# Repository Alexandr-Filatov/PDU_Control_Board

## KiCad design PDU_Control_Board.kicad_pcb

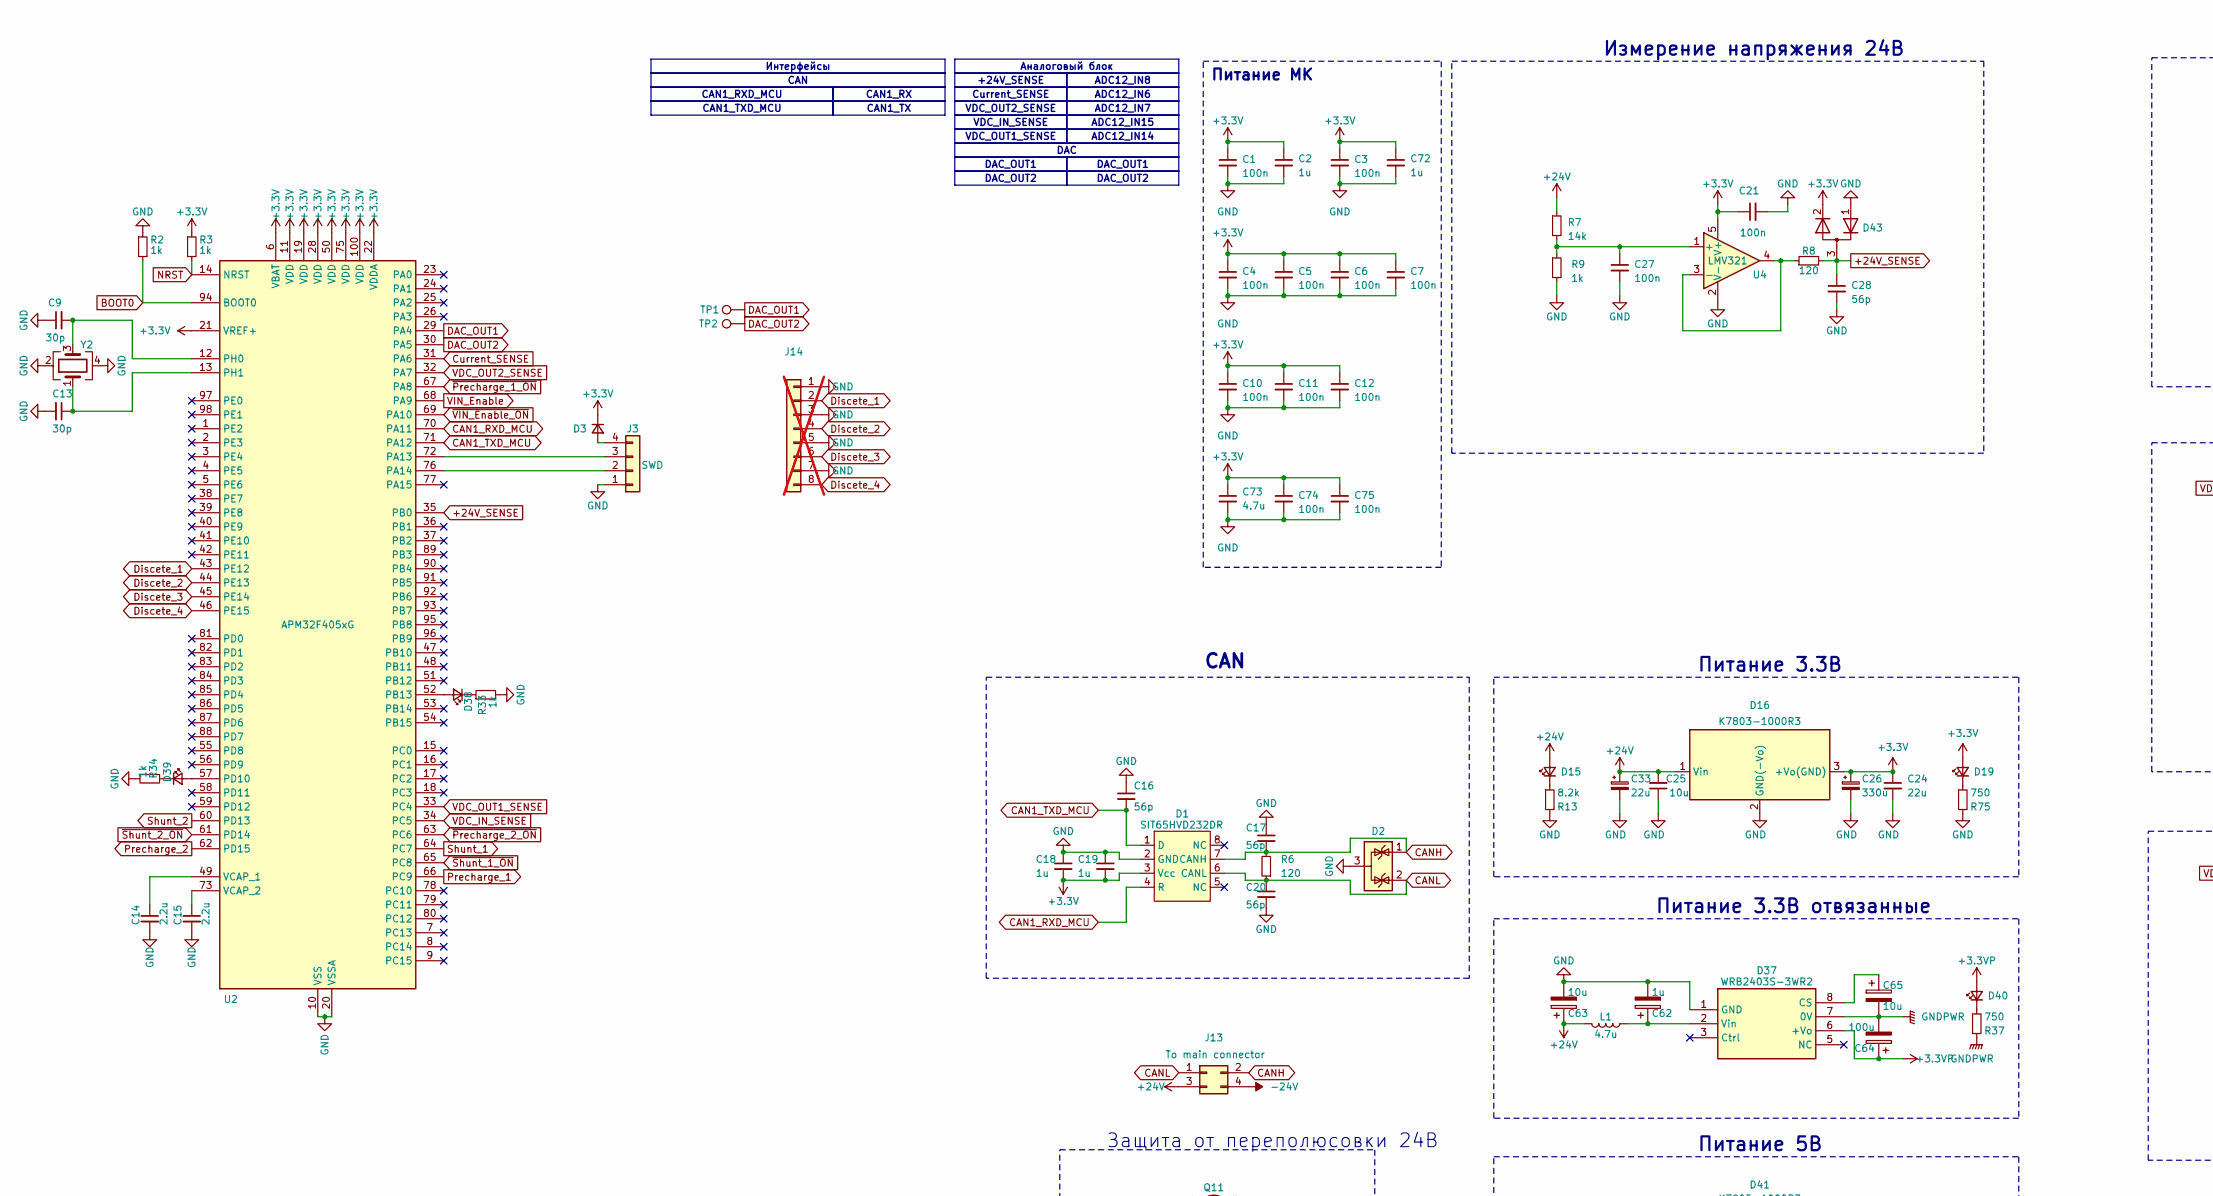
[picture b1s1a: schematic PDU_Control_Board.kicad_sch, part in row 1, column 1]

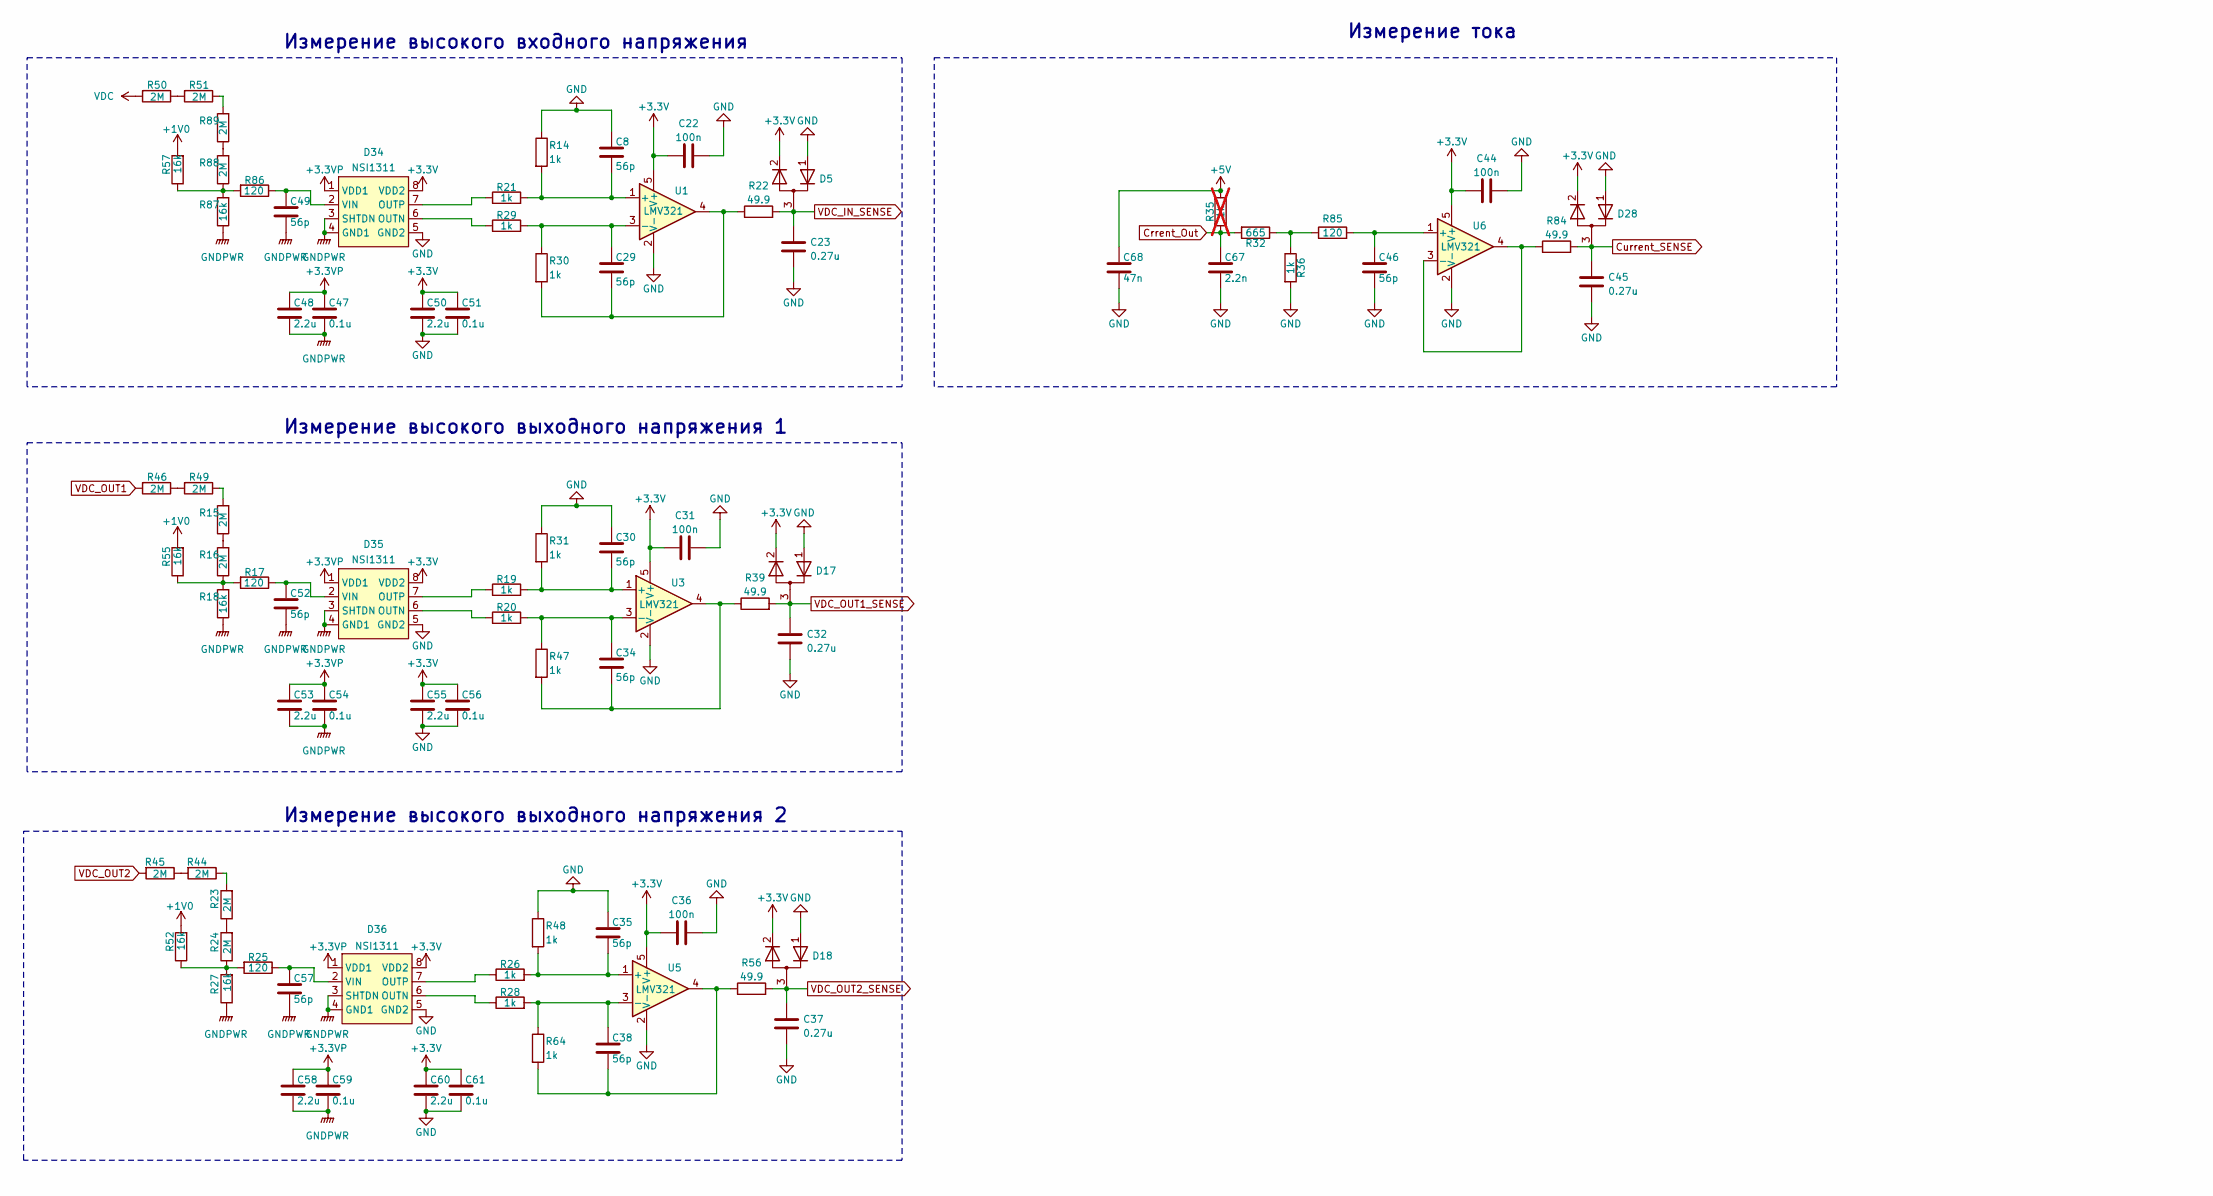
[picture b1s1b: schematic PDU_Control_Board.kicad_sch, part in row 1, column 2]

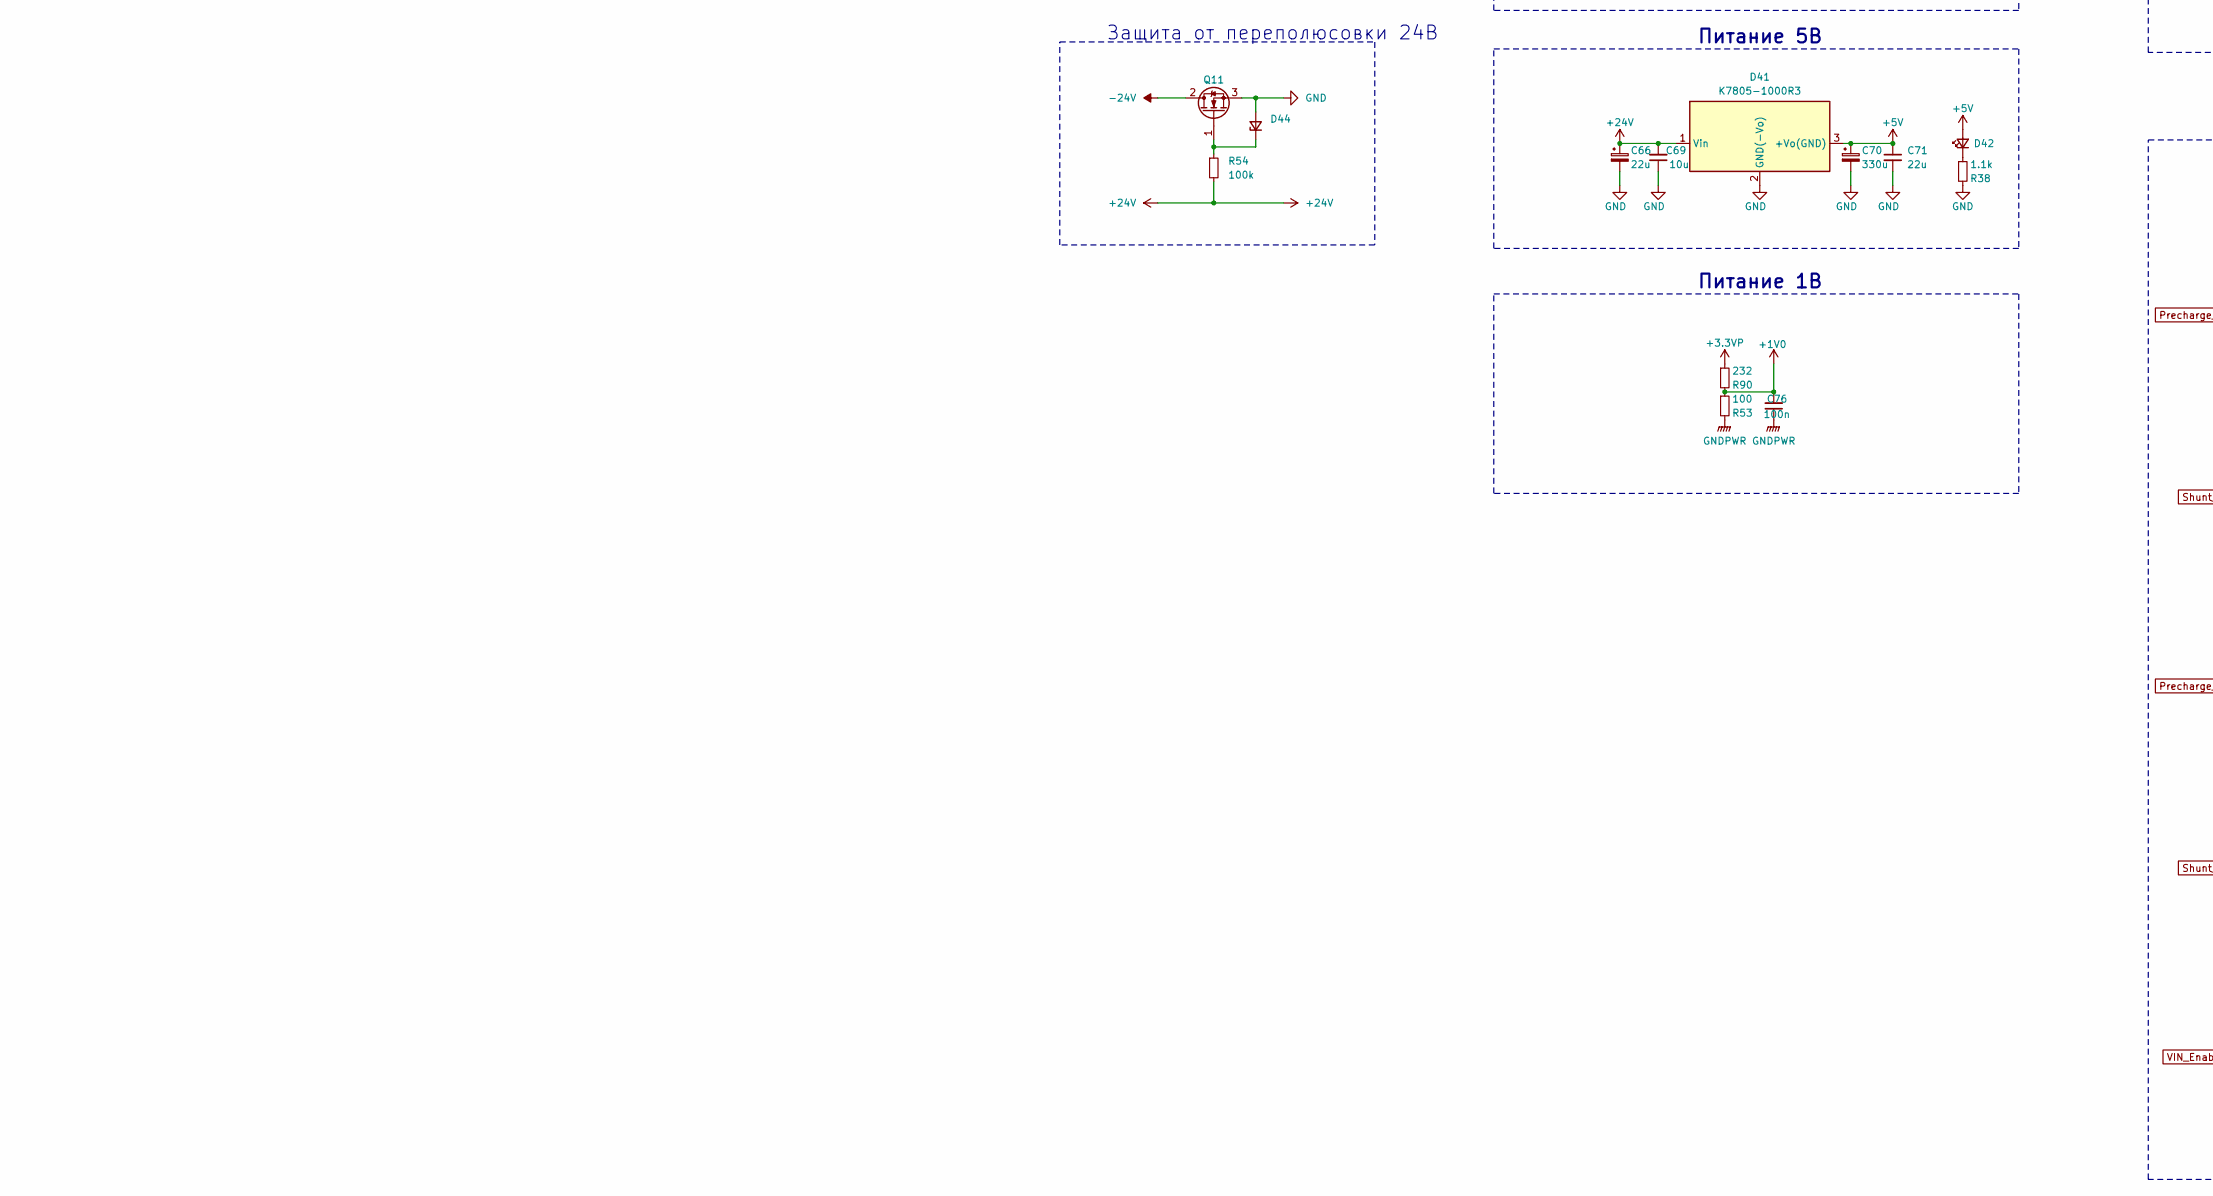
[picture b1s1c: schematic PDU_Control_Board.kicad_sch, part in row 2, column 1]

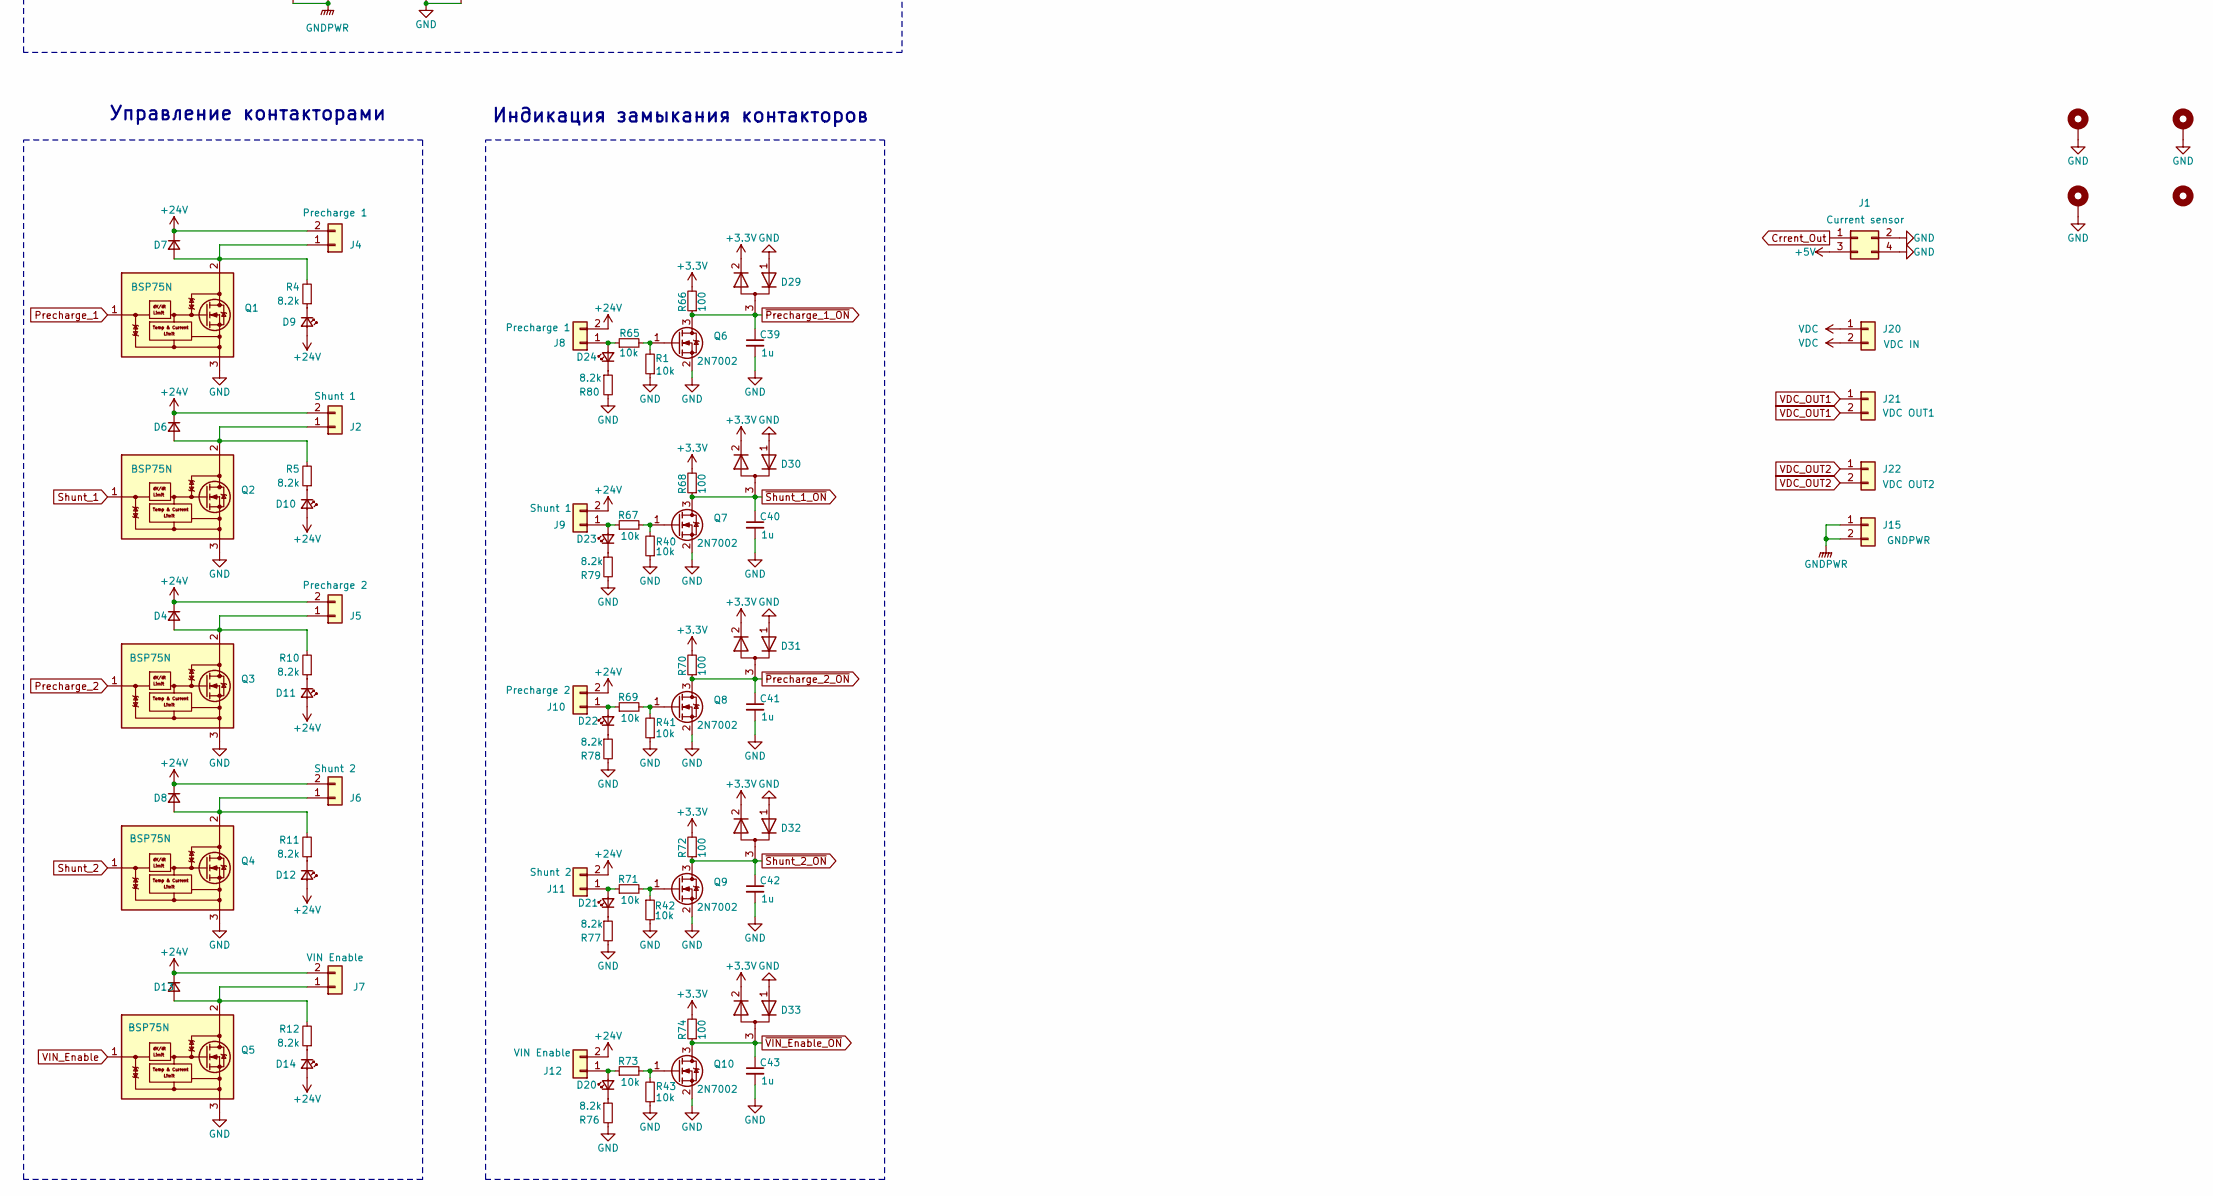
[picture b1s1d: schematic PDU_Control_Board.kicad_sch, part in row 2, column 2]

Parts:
C1, C3, C4, C5, C6, C7, C10, C11, C12, C21, C22, C27, C31, C36, C44, C74, C75, C76: 100n; C_0805_2012Metric_Pad1.18x1.45mm_HandSolder
C2, C18, C19, C39, C40, C41, C42, C43, C72: 1u; C_0805_2012Metric_Pad1.18x1.45mm_HandSolder
C8, C16, C17, C20, C28, C29, C30, C34, C35, C38, C46, C49, C52, C57: 56p; C_0805_2012Metric_Pad1.18x1.45mm_HandSolder
C9, C13: 30p; C_0805_2012Metric_Pad1.18x1.45mm_HandSolder
C14, C15, C48, C50, C53, C55, C58, C60: 2.2u; C_0805_2012Metric_Pad1.18x1.45mm_HandSolder
C23, C32, C37, C45: 0.27u; C_0805_2012Metric_Pad1.18x1.45mm_HandSolder
C24, C71: 22u; C_1210_3225Metric_Pad1.33x2.70mm_HandSolder
C25, C69: 10u; C_1210_3225Metric_Pad1.33x2.70mm_HandSolder
C26, C70: 330u; CP_EIA-6032-28_Kemet-C_Pad2.25x2.35mm_HandSolder
C33, C66: 22u; CP_EIA-7343-43_Kemet-X_Pad2.25x2.55mm_HandSolder
C47, C51, C54, C56, C59, C61: 0.1u; C_0805_2012Metric_Pad1.18x1.45mm_HandSolder
C62: 1u; CP_EIA-6032-28_Kemet-C_Pad2.25x2.35mm_HandSolder
C63: 10u; CP_EIA-7360-38_Kemet-E_Pad2.25x4.25mm_HandSolder
C64: 100u; CP_EIA-3528-21_Kemet-B_Pad1.50x2.35mm_HandSolder
C65: 10u; CP_EIA-3528-21_Kemet-B_Pad1.50x2.35mm_HandSolder
C67: 2.2n; C_0805_2012Metric_Pad1.18x1.45mm_HandSolder
C68: 47n; C_0805_2012Metric_Pad1.18x1.45mm_HandSolder
C73: 4.7u; C_0805_2012Metric_Pad1.18x1.45mm_HandSolder
D1: SOIC-8_3.9x4.9mm_P1.27mm
D2, D5, D17, D18, D28, D29, D30, D31, D32, D33, D43: SOT-23
D3: D_SOD-323_HandSoldering
D4, D6, D7, D8, D13: D_SMA_Handsoldering
D9, D10, D11, D12, D14, D15, D19, D20, D21, D22, D23, D24, D38, D39, D40, D42: LED_0805_2012Metric
D16, D41: K78xx-1000R3
D34, D35, D36: SOIC-8_7.5x5.85mm_P1.27mm
D37: WRB_S-3WR2
D44: D_SOD-123
H1, H2, H3: MountingHole_Pad; MountingHole_4.3mm_M4_Pad_Via
H4: MountingHole; MountingHole_4.3mm_M4
J1, J13: Molex_Mini-Fit_Jr_5566-04A_2x02_P4.20mm_Vertical
J2, J4, J5, J6, J7, J8, J9, J10, J11, J12, J15, J20, J21, J22: Mini-Fit_01x02_Vertical
J3: PinHeader_1x04_P2.54mm_Vertical
J14: PinHeader_2x04_P2.54mm_Vertical; not fitted
L1: 4.7u; L_1812_4532Metric_Pad1.30x3.40mm_HandSolder
Q1, Q2, Q3, Q4, Q5: SOT-223
Q6, Q7, Q8, Q9, Q10: SOT-23
Q11: TO-252-2
R1, R40, R41, R42, R43, R65, R67, R69, R71, R73: 10k; R_0805_2012Metric_Pad1.20x1.40mm_HandSolder
R2, R3, R9, R14, R19, R20, R21, R26, R28, R29, R30, R31, R33, R34, R36, R47, R48, R64: 1k; R_0805_2012Metric_Pad1.20x1.40mm_HandSolder
R4, R5, R10, R11, R12, R13, R76, R77, R78, R79, R80: 8.2k; R_0805_2012Metric_Pad1.20x1.40mm_HandSolder
R6, R8, R17, R25, R85, R86: 120; R_0805_2012Metric_Pad1.20x1.40mm_HandSolder
R7: 14k; R_0805_2012Metric_Pad1.20x1.40mm_HandSolder
R15, R16, R23, R24, R44, R45, R46, R49, R50, R51, R88, R89: 2M; R_1206_3216Metric
R18, R27, R52, R55, R57, R87: 16k; R_1206_3216Metric
R22, R39, R56, R84: 49.9; R_0805_2012Metric_Pad1.20x1.40mm_HandSolder
R32: 665; R_0805_2012Metric_Pad1.20x1.40mm_HandSolder
R35: 1k; R_0805_2012Metric_Pad1.20x1.40mm_HandSolder; not fitted
R37, R75: 750; R_0805_2012Metric_Pad1.20x1.40mm_HandSolder
R38: 1.1k; R_0805_2012Metric_Pad1.20x1.40mm_HandSolder
R53, R66, R68, R70, R72, R74: 100; R_0805_2012Metric_Pad1.20x1.40mm_HandSolder
R54: 100k; R_0805_2012Metric_Pad1.20x1.40mm_HandSolder
R90: 232; R_0805_2012Metric_Pad1.20x1.40mm_HandSolder
TP1, TP2: TestPoint; TestPoint_Loop_D1.80mm_Drill1.0mm_Beaded
U1, U3, U4, U5, U6: SOT-23-5
U2: LQFP-100_14x14mm_P0.5mm
Y2: Crystal_SMD_SeikoEpson_FA238-4Pin_3.2x2.5mm

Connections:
+1V0: C76.2, R52.2, R53.1, R55.2, R57.2, R90.2
+3.3V: C1.1, C2.1, C3.1, C4.1, C5.1, C6.1, C7.1, C10.1, C11.1, C12.1, C18.2, C19.2, C21.1, C22.1, C24.1, C26.1, C31.1, C36.1, C44.1, C50.2, C51.1, C55.2, C56.1, C60.2, C61.1, C72.1, C73.1, C74.1, C75.1, D1.3 (Vcc), D3.1 (K), D5.2 (K), D16.3 (+Vo(GND)), D17.2 (K), D18.2 (K), D19.2 (A), D28.2 (K), D29.2 (K), D30.2 (K), D31.2 (K), D32.2 (K), D33.2 (K), D34.8 (VDD2), D35.8 (VDD2), D36.8 (VDD2), D43.2 (K), R3.1, R66.2, R68.2, R70.2, R72.2, R74.2, U1.5 (V+), U2.6 (VBAT), U2.11 (VDD), U2.19 (VDD), U2.21 (VREF+), U2.22 (VDDA), U2.28 (VDD), U2.50 (VDD), U2.75 (VDD), U2.100 (VDD), U3.5 (V+), U4.5 (V+), U5.5 (V+), U6.5 (V+)
+3.3VP: C47.1, C48.2, C53.2, C54.1, C58.2, C59.1, C64.1, D34.1 (VDD1), D35.1 (VDD1), D36.1 (VDD1), D37.6 (+Vo), D40.2 (A), R90.1
+5V: C68.1, C70.1, C71.1, D41.3 (+Vo(GND)), D42.2 (A), J1.3, R35.2
+24V: C25.2, C33.1, C63.1, C66.1, C69.2, D4.1 (K), D6.1 (K), D7.1 (K), D8.1 (K), D9.2 (A), D10.2 (A), D11.2 (A), D12.2 (A), D13.1 (K), D14.2 (A), D15.2 (A), D16.1 (Vin), D41.1 (Vin), J2.2, J4.2, J5.2, J6.2, J7.2, J8.2, J9.2, J10.2, J11.2, J12.2, J13.3, L1.1, R7.1, R54.2
+24V_SENSE: C28.1, D43.3 (common), R8.2, U2.35 (PB0)
-24V: J13.4, Q11.2 (D)
BOOT0: R2.2, U2.94 (BOOT0)
CAN1_RXD_MCU: D1.4 (R), U2.70 (PA11)
CAN1_TXD_MCU: C16.2, D1.1 (D), U2.71 (PA12)
CANH: C17.2, D1.7 (CANH), D2.1 (K), J13.2, R6.2
CANL: C20.1, D1.6 (CANL), D2.2 (K), J13.1, R6.1
Crrent_Out: C67.1, J1.1, R32.2, R35.1
Current_SENSE: C45.1, D28.3 (common), R84.2, U2.31 (PA6)
DAC_OUT1: TP1.1, U2.29 (PA4)
DAC_OUT2: TP2.1, U2.30 (PA5)
Discete_1: J14.2, U2.43 (PE12)
Discete_2: J14.4, U2.44 (PE13)
Discete_3: J14.6, U2.45 (PE14)
Discete_4: J14.8, U2.46 (PE15)
GND: C1.2, C2.2, C3.2, C4.2, C5.2, C6.2, C7.2, C8.1, C9.1, C10.2, C11.2, C12.2, C13.2, C14.2, C15.2, C16.1, C17.1, C18.1, C19.1, C20.2, C21.2, C22.2, C23.2, C24.2, C25.1, C26.2, C27.2, C28.2, C30.1, C31.2, C32.2, C33.2, C35.1, C36.2, C37.2, C39.2, C40.2, C41.2, C42.2, C43.2, C44.2, C45.2, C46.2, C50.1, C51.2, C55.1, C56.2, C60.1, C61.2, C62.2, C63.2, C66.2, C67.2, C68.2, C69.1, C70.2, C71.2, C72.2, C73.2, C74.2, C75.2, D1.2 (GND), D2.3 (A), D5.1 (A), D16.2 (GND(-Vo)), D17.1 (A), D18.1 (A), D28.1 (A), D29.1 (A), D30.1 (A), D31.1 (A), D32.1 (A), D33.1 (A), D34.5 (GND2), D35.5 (GND2), D36.5 (GND2), D37.1 (GND), D41.2 (GND(-Vo)), D43.1 (A), D44.2 (A), H1.1, H2.1, H3.1, J1.2, J1.4, J3.1, J14.1, J14.3, J14.5, J14.7, Q1.3 (S), Q1.4 (S), Q2.3 (S), Q2.4 (S), Q3.3 (S), Q3.4 (S), Q4.3 (S), Q4.4 (S), Q5.3 (S), Q5.4 (S), Q6.2 (S), Q7.2 (S), Q8.2 (S), Q9.2 (S), Q10.2 (S), Q11.3 (S), R1.1, R2.1, R9.2, R13.2, R14.1, R31.1, R33.2, R34.2, R36.2, R38.2, R40.1, R41.1, R42.2, R43.1, R48.1, R75.2, R76.2, R77.2, R78.2, R79.2, R80.2, U1.2 (V-), U2.10 (VSS), U2.20 (VSSA), U2.27 (VSS), U2.74 (VSS), U2.99 (VSS), U3.2 (V-), U4.2 (V-), U5.2 (V-), U6.2 (V-), Y2.2, Y2.4
GNDPWR: C47.2, C48.1, C49.2, C52.2, C53.1, C54.2, C57.2, C58.1, C59.2, C64.2, C65.2, C76.1, D34.3 (SHTDN), D34.4 (GND1), D35.3 (SHTDN), D35.4 (GND1), D36.3 (SHTDN), D36.4 (GND1), D37.7 (0V), J15.1, J15.2, R18.1, R27.1, R37.2, R53.2, R87.1
NRST: R3.2, U2.14 (NRST)
unnamed: C29.2, R22.1, R30.2, U1.4
unnamed: C34.2, R39.1, R47.2, U3.4
unnamed: C38.2, R56.1, R64.2, U5.4
unnamed: D3.2 (A), J3.4
unnamed: D4.2 (A), J5.1, Q3.2 (D), R10.2
unnamed: D6.2 (A), J2.1, Q2.2 (D), R5.2
unnamed: D7.2 (A), J4.1, Q1.2 (D), R4.2
unnamed: D8.2 (A), J6.1, Q4.2 (D), R11.2
unnamed: D9.1 (K), R4.1
unnamed: D10.1 (K), R5.1
unnamed: D11.1 (K), R10.1
unnamed: D12.1 (K), R11.1
unnamed: D13.2 (A), J7.1, Q5.2 (D), R12.2
unnamed: D14.1 (K), R12.1
unnamed: D15.1 (K), R13.1
unnamed: D19.1 (K), R75.1
unnamed: D20.2 (A), J12.1, R73.1
unnamed: D20.1 (K), R76.1
unnamed: D21.2 (A), J11.1, R71.1
unnamed: D21.1 (K), R77.1
unnamed: D22.2 (A), J10.1, R69.1
unnamed: D22.1 (K), R78.1
unnamed: D23.2 (A), J9.1, R67.1
unnamed: D23.1 (K), R79.1
unnamed: D24.2 (A), J8.1, R65.1
unnamed: D24.1 (K), R80.1
unnamed: D34.6 (OUTN), R29.1
unnamed: D34.7 (OUTP), R21.1
unnamed: C49.1, D34.2 (VIN), R86.1
unnamed: D35.6 (OUTN), R20.1
unnamed: D35.7 (OUTP), R19.1
unnamed: C52.1, D35.2 (VIN), R17.1
unnamed: D36.6 (OUTN), R28.1
unnamed: D36.7 (OUTP), R26.1
unnamed: C57.1, D36.2 (VIN), R25.1
unnamed: C65.1, D37.8 (CS)
unnamed: C62.1, D37.2 (Vin), L1.2
unnamed: D38.2 (A), U2.52 (PB13)
unnamed: D38.1 (K), R33.1
unnamed: D39.2 (A), U2.57 (PD10)
unnamed: D39.1 (K), R34.1
unnamed: D40.1 (K), R37.1
unnamed: D42.1 (K), R38.1
unnamed: D44.1 (K), Q11.1 (G), R54.1
unnamed: J3.2, U2.76 (PA14)
unnamed: J3.3, U2.72 (PA13)
unnamed: Q6.1 (G), R1.2, R65.2
unnamed: Q7.1 (G), R40.2, R67.2
unnamed: Q8.1 (G), R41.2, R69.2
unnamed: Q9.1 (G), R42.1, R71.2
unnamed: Q10.1 (G), R43.2, R73.2
unnamed: R15.1, R16.2
unnamed: R15.2, R49.1
unnamed: R16.1, R17.2, R18.2, R55.1
unnamed: R23.1, R24.2
unnamed: R23.2, R44.1
unnamed: R24.1, R25.2, R27.2, R52.1
unnamed: R32.1, R36.1, R85.1
unnamed: R44.2, R45.1
unnamed: R46.1, R49.2
unnamed: R50.1, R51.2
unnamed: R51.1, R89.2
unnamed: R57.1, R86.2, R87.2, R88.1
unnamed: R88.2, R89.1
unnamed: C8.2, R14.2, R21.2, U1.1 (+)
unnamed: C29.1, R29.2, R30.1, U1.3 (-)
unnamed: C9.2, U2.12 (PH0), Y2.3
unnamed: C13.1, U2.13 (PH1), Y2.1
unnamed: C14.1, U2.49 (VCAP_1)
unnamed: C15.1, U2.73 (VCAP_2)
unnamed: C30.2, R19.2, R31.2, U3.1 (+)
unnamed: C34.1, R20.2, R47.1, U3.3 (-)
unnamed: C27.1, R7.2, R9.1, U4.1 (+)
unnamed: R8.1, U4.3 (-), U4.4
unnamed: C35.2, R26.2, R48.2, U5.1 (+)
unnamed: C38.1, R28.2, R64.1, U5.3 (-)
unnamed: C46.1, R85.2, U6.1 (+)
unnamed: R84.1, U6.3 (-), U6.4
Precharge_1: Q1.1 (G), U2.66 (PC9)
Precharge_2: Q3.1 (G), U2.62 (PD15)
Shunt_1: Q2.1 (G), U2.64 (PC7)
Shunt_2: Q4.1 (G), U2.60 (PD13)
VDC: J20.1, J20.2, R50.2
VDC_IN_SENSE: C23.1, D5.3 (common), R22.2, U2.34 (PC5)
VDC_OUT1: J21.1, J21.2, R46.2
VDC_OUT1_SENSE: C32.1, D17.3 (common), R39.2, U2.33 (PC4)
VDC_OUT2: J22.1, J22.2, R45.2
VDC_OUT2_SENSE: C37.1, D18.3 (common), R56.2, U2.32 (PA7)
VIN_Enable: Q5.1 (G), U2.68 (PA9)
~Precharge_1_ON: C39.1, D29.3 (common), Q6.3 (D), R66.1, U2.67 (PA8)
~Precharge_2_ON: C41.1, D31.3 (common), Q8.3 (D), R70.1, U2.63 (PC6)
~Shunt_1_ON: C40.1, D30.3 (common), Q7.3 (D), R68.1, U2.65 (PC8)
~Shunt_2_ON: C42.1, D32.3 (common), Q9.3 (D), R72.1, U2.61 (PD14)
~VIN_Enable_ON: C43.1, D33.3 (common), Q10.3 (D), R74.1, U2.69 (PA10)

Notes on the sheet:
Измерение напряжения 24В
Питание 5В
Питание 3.3В
Питание МК
Измерение высокого выходного напряжения 1
Измерение высокого входного напряжения
Питание 1В
Управление контакторами
Индикация замыкания контакторов
Измерение высокого выходного напряжения 2
Питание 3.3В отвязанные
Защита от переполюсовки 24В
CAN
Измерение тока
DAC_OUT2
ADC12_IN7
Аналоговый блок
VDC_IN_SENSE
ADC12_IN15
DAC_OUT1
VDC_OUT2_SENSE
DAC
CAN1_RXD_MCU
ADC12_IN14
CAN1_RX
CAN1_TXD_MCU
CAN1_TX
DAC_OUT2
ADC12_IN8
Интерфейсы
ADC12_IN6
VDC_OUT1_SENSE
Current_SENSE
+24V_SENSE

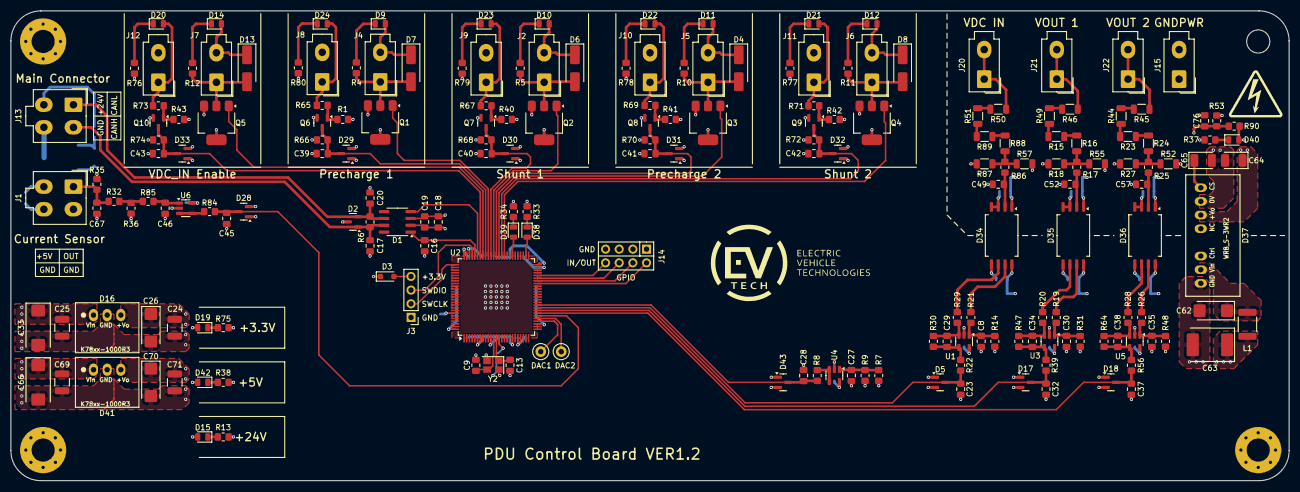
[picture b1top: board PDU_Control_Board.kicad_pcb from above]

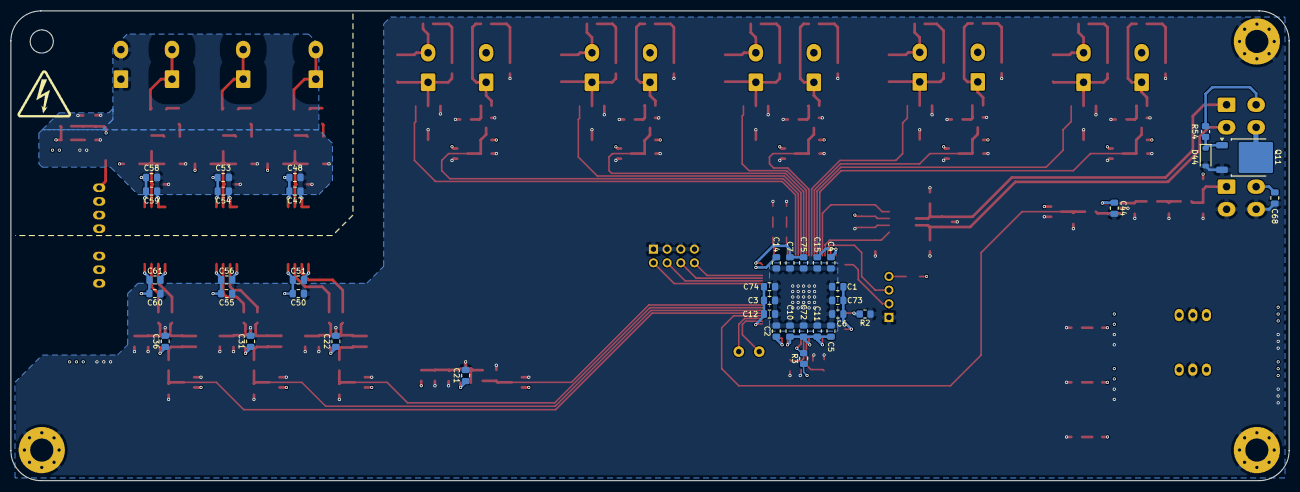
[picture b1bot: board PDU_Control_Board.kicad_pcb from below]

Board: 4 copper layers, 237.7 x 87.4 mm, 241 parts (39 on the bottom side), 117 nets.

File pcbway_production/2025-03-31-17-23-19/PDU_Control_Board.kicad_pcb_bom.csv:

Designator,Quantity,Value,Footprint,Package,MPN,DNP,Mount_Type,Description,Product Name,Description P/N,Sim.Device,Sim.Pins,Purpose,Replacement
"C1, C10, C11, C12, C21, C22, C27, C3, C31, C36, C4, C44, C5, C6, C7, C74, C75",17,100n,C_0805_2012Metric_Pad1.18x1.45mm_HandSolder,,,,smt,,,,,,,
"C13, C9",2,30p,C_0805_2012Metric_Pad1.18x1.45mm_HandSolder,,,,smt,,,,,,,
"C14, C15, C48, C50, C53, C55, C58, C60",8,2.2u,C_0805_2012Metric_Pad1.18x1.45mm_HandSolder,,,,smt,,,,,,,
"C16, C17, C20, C28, C29, C30, C34, C35, C38, C46, C49, C52, C57, C8",14,56p,C_0805_2012Metric_Pad1.18x1.45mm_HandSolder,,,,smt,,,,,,,
"C18, C19, C2, C39, C40, C41, C42, C43, C72",9,1u,C_0805_2012Metric_Pad1.18x1.45mm_HandSolder,,,,smt,,,,,,,
"C23, C32, C37, C45",4,0.27u,C_0805_2012Metric_Pad1.18x1.45mm_HandSolder,,,,smt,,,,,,,
"C24, C71",2,22u,C_1210_3225Metric_Pad1.33x2.70mm_HandSolder,,,,smt,16V,,,,,,
"C25, C69",2,10u,C_1210_3225Metric_Pad1.33x2.70mm_HandSolder,,,,smt,50V,,,,,,
"C26, C70",2,330u,CP_EIA-6032-28_Kemet-C_Pad2.25x2.35mm_HandSolder,,,,smt,"Polarized capacitor, small symbol",CA45-C6R3K337T,,,,,
"C33, C66",2,22u,CP_EIA-7343-43_Kemet-X_Pad2.25x2.55mm_HandSolder,,,,smt,"Polarized capacitor, small symbol",CA45L-E050K226TE400,,,,,
"C47, C51, C54, C56, C59, C61",6,0.1u,C_0805_2012Metric_Pad1.18x1.45mm_HandSolder,,,,smt,,,,,,,
C62,1,1u,CP_EIA-6032-28_Kemet-C_Pad2.25x2.35mm_HandSolder,,,,smt,Polarized capacitor,293D105X9050C2TE3,,,,,
C63,1,10u,CP_EIA-7360-38_Kemet-E_Pad2.25x4.25mm_HandSolder,,,,smt,Polarized capacitor,293D106X9050E2TE3,,,,,
C64,1,100u,CP_EIA-3528-21_Kemet-B_Pad1.50x2.35mm_HandSolder,,,,smt,Polarized capacitor,293D107X96R3B2TE3,,,,,
C65,1,10u,CP_EIA-3528-21_Kemet-B_Pad1.50x2.35mm_HandSolder,,,,smt,Polarized capacitor,293D106X96R3B2TE3,,,,,
C67,1,2.2n,C_0805_2012Metric_Pad1.18x1.45mm_HandSolder,,,,smt,,,,,,,
C68,1,47n,C_0805_2012Metric_Pad1.18x1.45mm_HandSolder,,,,smt,,,,,,,
C73,1,4.7u,C_0805_2012Metric_Pad1.18x1.45mm_HandSolder,,,,smt,,,,,,,
D1,1,~,SOIC-8_3.9x4.9mm_P1.27mm,,,,smt,,SIT65HVD232DR,CAN interface,,,,
"D10, D11, D12, D14, D15, D19, D20, D21, D22, D23, D24, D25, D26, D27, D38, D39, D40, D42, D9",19,~,LED_0805_2012Metric,,,,smt,"Light emitting diode, small symbol","[D9]FYLS-0805UBC; [D40,D42]FYLS-0805UYC","[D9]Blue LED; [D40,D42]Yellow LED",,,,
"D13, D4, D6, D7, D8",5,~,D_SMA_Handsoldering,,,,smt,"Diode, small symbol",RS1B,Fast recovery diode,D,1=K 2=A,,
"D16, D41",2,~,K78xx-1000R3,,,,tht,,[D16]K7803-1000R3; [D41]K7805-1000R3,DC/DC converter ,,,,
"D17, D18, D2, D28, D29, D30, D31, D32, D33, D43, D5, Q10, Q6, Q7, Q8, Q9",16,~,SOT-23,,,,smt,"[D28,D29,D30,D31,D32,D33,D43,D5]Dual diode, anode/cathode/center; [D2]Dual Line CAN Bus Protector, 24Vrwm; [Q10,Q6,Q7,Q8,Q9]0.115A Id, 60V Vds, N-Channel MOSFET, SOT-23","[D28,D29,D30,D31,D32,D33,D43,D5]BAT54S; [D2]PESD2CAN; [Q10,Q6,Q7,Q8,Q9]2N7002","[D28,D29,D30,D31,D32,D33,D43,D5]Schottky barrier diode; [D2]Dual Line CAN Bus Protector, 24Vrwm; [Q10,Q6,Q7,Q8,Q9]N_channel MOSFET",,,,
D3,1,~,D_SOD-323_HandSoldering,,,,smt,,BAS416,Diode,D,1=K 2=A,,
"D34, D35, D36",3,~,SOIC-8_7.5x5.85mm_P1.27mm,,,,smt,,NSI1311,Isolated amplifier,,,,
D37,1,~,WRB_S-3WR2,,,,tht,,WRB2403S-3WR2,DC/DC converter ,,,,
"J1, J13",2,~,Molex_Mini-Fit_Jr_5566-04A_2x02_P4.20mm_Vertical,,,,tht,"Generic connector, double row, 02x02, odd/even pin numbering scheme (row 1 odd numbers, row 2 even numbers), script generated (kicad-library-utils/schlib/autogen/connector/)",DS1073-01-2x2-MVT6,Connector,,,[J1]Current sensor; [J13]To main connector,
"J10, J11, J12, J2, J20, J21, J22, J4, J5, J6, J7, J8, J9",13,~,Mini-Fit_01x02_Vertical,,,,tht,"Generic connector, single row, 01x02, script generated (kicad-library-utils/schlib/autogen/connector/)",DS1073-01-2x1-MVT6,Connector,,,[J5]Precharge 2; [J6]Shunt 2; [J7]VIN Enable; [J9]Shunt 1; [J20]VDC IN; [J21]VDC OUT1; [J22]VDC OUT2; [J8]Precharge 1,
J14,1,~,PinHeader_2x04_P2.54mm_Vertical,,,Yes,tht,"Generic connector, single row, 01x08, script generated (kicad-library-utils/schlib/autogen/connector/)",,,,,,
J3,1,~,PinHeader_1x04_P2.54mm_Vertical,,,,tht,,PLS-4,Connector,,,SWD,DS-1021-1x4
L1,1,4.7u,L_1812_4532Metric_Pad1.30x3.40mm_HandSolder,,,,smt,Inductor,NLC453232T-4R7K-PF,,,,,
"Q1, Q2, Q3, Q4, Q5",5,~,SOT-223,,,,smt,"Self-Protected Low Side Driver with Temperature and Current Limit, SOT−223",BSP75N,"Self-Protected Low Side Driver with Temperature and Current Limit, SOT−223",,,,
"R1, R40, R41, R42, R43, R65, R67, R69, R71, R73",10,10k,R_0805_2012Metric_Pad1.20x1.40mm_HandSolder,,,,smt,"Resistor, small symbol",,,,,,
"R10, R11, R12, R13, R4, R5, R76, R77, R78, R79, R80",11,5.1k,R_0805_2012Metric_Pad1.20x1.40mm_HandSolder,,,,smt,"Resistor, small symbol",,,,,,
"R14, R19, R2, R20, R21, R26, R28, R29, R3, R30, R31, R33, R34, R36, R47, R48, R64, R9",18,1k,R_0805_2012Metric_Pad1.20x1.40mm_HandSolder,,,,smt,"Resistor, small symbol",,,,,,
"R15, R16, R23, R24, R44, R45, R46, R49, R50, R51, R88, R89",12,23.7k,R_1206_3216Metric,,,,smt,,,,,,,
"R17, R25, R6, R8, R85, R86",6,120,R_0805_2012Metric_Pad1.20x1.40mm_HandSolder,,,,smt,,,,,,,
"R18, R27, R87",3,210,R_1206_3216Metric,,,,smt,,,,,,,
"R22, R39, R56, R84",4,49.9,R_0805_2012Metric_Pad1.20x1.40mm_HandSolder,,,,smt,,,,,,,
R32,1,665,R_0805_2012Metric_Pad1.20x1.40mm_HandSolder,,,,smt,,,,,,,
R35,1,1k,R_0805_2012Metric_Pad1.20x1.40mm_HandSolder,,,Yes,smt,,,,,,,
"R37, R75",2,750,R_0805_2012Metric_Pad1.20x1.40mm_HandSolder,,,,smt,"Resistor, small symbol",,,,,,
R38,1,1.1k,R_0805_2012Metric_Pad1.20x1.40mm_HandSolder,,,,smt,"Resistor, small symbol",,,,,,
"R66, R68, R70, R72, R74",5,100,R_0805_2012Metric_Pad1.20x1.40mm_HandSolder,,,,smt,"Resistor, small symbol",,,,,,
R7,1,14k,R_0805_2012Metric_Pad1.20x1.40mm_HandSolder,,,,smt,,,,,,,
"R81, R82, R83",3,100k,R_1206_3216Metric_Pad1.30x1.75mm_HandSolder,,,,smt,"Resistor, small symbol",,,,,,
"TP1, TP2",2,TestPoint,TestPoint_Loop_D1.80mm_Drill1.0mm_Beaded,,,,tht,test point,,,,,,
"U1, U3, U4, U5, U6",5,~,SOT-23-5,,,,smt,"Low-Voltage Rail-to-Rail Output Operational Amplifiers, SOT-23-5/SC-70-5",LMV321,"Low-Voltage Rail-to-Rail Output Operational Amplifiers, SOT-23-5/SC-70-5",,,,
U2,1,~,LQFP-100_14x14mm_P0.5mm,,,,smt,,APM32F405xG,uController,,,,
Y2,1,~,Crystal_SMD_SeikoEpson_FA238-4Pin_3.2x2.5mm,,,,smt,,X322516MOB4SI,Crystal,,,,

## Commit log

2025-03-03 VER1.0: добавил в схему индикацию замыкания
2025-03-04 VER1.0: разместил все на плате
2025-03-06 VER1.0: добавил на плату все контакторы
2025-03-06 VER1.0: сделал отвязанное измерение напряжения
2025-03-11 VER1.0: обрезал плату
2025-03-13 VER1.0: разместил все компоненты на плате
2025-03-18 VER1.0: трассировал все дорожки и полигоны
2025-03-19 VER1.0: подвинул крепежные отверстия
2025-03-19 VER2.0: zero commit
2025-03-19 VER2.0: добавил зарядные резисторы
2025-03-20 VER2.0: выдвинул разъём вперед платы
2025-03-22 VER3: zero commit
2025-03-24 VER3.0: сделал предварительную расстановку платы
2025-03-25 VER3.0: плата готова
2025-03-26 VER3.0: добавил шелкографию на заднюю сторону
2025-03-26 VER3.0: добавил гербера
2025-03-28 VER3.0: разобрался с бомом, добавил дискреты, DAC, поменял обратную свзять от контакторов, удлинил цепочку измерения высокого
2025-03-31 VER3.0: заказал плату в резоните
2025-03-31 VER3.0: добавил закупочный лист
2025-04-30 VER1.1: обновил полигоны, закинул в резонит черновик
2025-05-21 VER1.1: добавил схему в доки
2025-06-05 VER1.1: добавил схему предзаряда и защиту от переполюсовки по 24В
2025-06-16 VER1.1: добавил резистор смещение в измерение шины DC
2025-06-18 VER1.1: исправленная по полигонам версия
2025-06-18 VER1.1: добавил схему по госту в доки
2025-06-18 VER1.1: добавил спецификацию по госту и 3д модели
2025-06-19 VER1.1: добавил сборочный чертеж в доки
2025-06-20 VER1.1: изменил спецификацию и рамку у СБ
2025-07-01 VER1.1: исправил сборочный
2025-07-03 VER1.1: исправил СБ
2025-07-10 VER1.1: исправил Э3
2025-07-10 VER1.1: исправил Э3 еще раз
2025-07-14 VER1.1: подправил BOM
2025-07-14 VER1.1: переименовал Э3
2025-07-15 VER1.1: переделал спецификацию в автокаде
2025-07-17 VER2.1: добавил расчет дросселя
2025-07-31 VER1.2: добавил защиту по высокому
2025-08-20 VER1.2: отправил в резонит
2025-08-21 VER1.2: добавил КД на диск
2025-11-12 VER1.2: исправил доки
2025-11-14 VER1.2: исправил ошибки в доках
